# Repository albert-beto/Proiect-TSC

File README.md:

# InkTime v6

InkTime v6 este o platformă wearable construită pentru autonomie mare și interacțiune discretă. Dispozitivul folosește un display e-paper, conectivitate Bluetooth Low Energy, senzori de mișcare, feedback haptic și alimentare dintr-un acumulator LiPo încărcat prin USB-C.

La nivel de arhitectură, tot sistemul este orchestrat de un **Nordic nRF52840**, care gestionează radio-ul, magistralele digitale și logica de power management.

---

## Ce face dispozitivul

InkTime v6 este gândit ca un smartwatch sau dispozitiv portabil cu consum redus, capabil să rămână activ perioade lungi de timp între încărcări.

Funcțiile principale sunt:

- afișare pe e-paper, cu consum aproape nul în stare statică;
- comunicație BLE;
- detecție de mișcare și numărare pași;
- feedback haptic;
- încărcare prin USB-C;
- monitorizare a stării bateriei.

---

## Diagramă bloc

---

## Nucleul sistemului

### nRF52840

Controlerul principal este **nRF52840**, un SoC cu ARM Cortex-M4F, memorie Flash de 1 MB, 256 KB RAM, radio 2.4 GHz multiprotocol și interfață USB 2.0 Full-Speed integrată.

Acesta a fost ales pentru că permite integrarea într-un singur cip a mai multor funcții importante:

- comunicație BLE 5.0;
- control al perifericelor pe I2C și SPI;
- suport USB nativ;
- moduri eficiente de consum redus.

Pentru tactare sunt folosite două cristale externe:

- `X1` — 32 MHz, pentru **HFCLK**;
- `X2` — 32.768 kHz, pentru **LFCLK**.

---

## Interfețe și periferice

### Display e-paper

Interfața principală a utilizatorului este un display e-paper conectat printr-un FPC cu 24 de pini (`J3`). Pentru că afișajul este bistabil, energia este consumată în principal în timpul actualizării, nu în perioada în care imaginea rămâne neschimbată.

Controlul acestui bloc este împărțit în trei părți.

#### 1. Semnale digitale

Comunicarea cu displayul se face printr-o interfață SPI și linii auxiliare:

- `MOSI`
- `SCK`
- `EPD_CS`
- `EPD_DC`
- `EPD_RST`
- `EPD_BUSY`

#### 2. Tensiuni bias pentru panou

Driverul displayului are nevoie de mai multe tensiuni specifice pentru matricea TFT. Acestea sunt obținute cu ajutorul unui mic boost converter și al unei rețele de diode Schottky și condensatoare.

Tensiunile generate sunt:

- `VGH`
- `VGL`
- `VSH`
- `VSL`

#### 3. Oprirea completă a alimentării displayului

Alimentarea de 3.3 V a ansamblului EPD poate fi întreruptă complet printr-un load switch realizat cu MOSFET-ul P-channel **DMG2305UX** (`Q1`). Acesta este comandat de semnalul `EPD_PWR`.

### Accelerometru

Pentru detectarea activității este folosit **BMA423** (`IC2`), un accelerometru digital pe 3 axe.

Rolurile sale în proiect sunt:

- detecția de mișcare;
- step counting;
- generarea de evenimente prin întreruperi.

Componenta este utilizată în **mod I2C**, iar pinul `CSB` este conectat la `VDDIO` pentru a forța această configurație. Cele două ieșiri de întrerupere, `INT1` și `INT2`, sunt rutate separat spre microcontroller.

### Haptic

Blocul de feedback haptic se bazează pe **DRV2605** (`IC1`), controlat pe I2C. Activarea sau dezactivarea lui se face din semnalul `HAPTIC_EN`, conectat la un GPIO al MCU-ului.

Ieșirile `OUT+` și `OUT−` merg direct spre actuatorul haptic.

### Butoane

Sunt implementate trei butoane fizice:

- `SW_UP`
- `SW_DN`
- `SW_ENT`

Fiecare este conectat la câte un GPIO și are:

- pull-up extern de 10 kΩ;
- circuit RC de debounce cu 1 µF la GND.

---

## Alimentare

### USB-C

Conectorul `J1` este un **USB Type-C** (`KH-TYPE-C-16P`) folosit pentru alimentare și pentru conexiunea USB 2.0. În layout sunt rutate doar liniile necesare proiectului.

### Protecție ESD

Pentru protejarea liniilor USB și CC este folosit **USBLC6-2SC6Y**, plasat aproape de conector.

### Încărcător Li-Po

Gestionarea încărcării acumulatorului este făcută de **BQ25180** (`IC4`).

Acest circuit oferă:

- configurare prin I2C;
- curent de încărcare programabil;
- semnalizare de evenimente prin pinul `PMIC_INT`;
- protecție termică.

### Fuel gauge

Monitorizarea bateriei este realizată de **MAX17048** (`U1`), care măsoară tensiunea celulei și estimează nivelul de încărcare.

În design:

- comunică pe magistrala I2C comună;
- folosește semnalul `ALERT` pentru notificări către MCU.

### Convertor DC/DC

Subsistemul de putere include și **RT6160AWSC** (`IC3`), folosit ca convertor DC/DC.

---

## Programare și debug

Pentru flash și depanare este prevăzut un conector **Tag-Connect TC2030-IDC** (`J2`), cu 6 pini, fără header montat permanent pe PCB.

Liniile expuse sunt:

- `VTREF (3.3V)`
- `SWDIO`
- `SWDCLK`
- `SWO`
- `nRESET`
- `GND`

Pe placă există și test pads dedicate:

- `TP_SWDIO`
- `TP_SWDCLK`
- `TP_SWO`
- `TP_RESET`
- `TP_3.3V`
- `TP_GND`

---

## Alocarea pinilor MCU

Mai jos este rezumat mapping-ul relevant pentru nRF52840.

| Pin nRF52840 | Rol | Tip | Observație |
|---|---|---|---|
| **P0.00** | Cristal 32.768 kHz | OSC | Pin dedicat LFXO |
| **P0.01** | Cristal 32.768 kHz | OSC | Pin dedicat LFXO |
| **P0.09** | neconectat | GPIO | rezervat |
| **P0.10** | neconectat | GPIO | rezervat |
| **P0.13** | `MOSI` spre EPD | SPIM | rutare scurtă spre zona displayului |
| **P0.14** | `SCK` spre EPD | SPIM | grupat cu `MOSI` |
| **P0.18** | reset extern | nRESET | pin dedicat |
| **P0.19** | `EPD_CS` | SPIM | asociat interfeței EPD |
| **P0.20** | `EPD_DC` | GPIO | control display |
| **P0.21** | `EPD_RST` | GPIO | reset display |
| **P0.22** | `SWO` | SWO | debug |
| **P0.23** | `EPD_BUSY` | GPIO input + INT | semnal status display |
| **P0.24** | `EPD_PWR` | GPIO | comandă load switch |
| **P0.25** | `HAPTIC_EN` | GPIO | enable pentru DRV2605 |
| **P0.26** | `SDA` | TWIM | magistrală I2C |
| **P0.27** | `SCL` | TWIM | magistrală I2C |
| **P0.28** | neconectat | analog | rezervat |
| **P0.29** | neconectat | GPIO | rezervat |
| **P0.30** | neconectat | GPIO | rezervat |
| **P0.31** | neconectat | GPIO | rezervat |
| **P1.00** | `PMIC_INT` | GPIO input + INT | evenimente de charging |
| **P1.01** | `SW_UP` | GPIO input | buton |
| **P1.02** | `SW_DN` | GPIO input | buton |
| **P1.03** | `SW_ENT` | GPIO input | buton |
| **P1.04** | `IMU_INT1` | GPIO input + INT | eveniment accelerometru |
| **P1.05** | `IMU_INT2` | GPIO input + INT | eveniment accelerometru |
| **P1.06** | `ALERT` | GPIO input + INT | alertă baterie |
| **P1.07** | EPD spre Q3 | GPIO / PWM | comandă auxiliară |
| **SWDCLK** | programare / debug | dedicat | SWD |
| **SWDIO** | programare / debug | dedicat | SWD |
| **VBUS** | detectare USB | USB PHY | sensing VBUS |
| **D+ / D−** | USB 2.0 FS | USB PHY | interfață USB |

---

## Consum și autonomie

### Curent estimat în standby

| Componentă | Curent tipic | Observații |
|---|---:|---|
| nRF52840 (System ON, RAM retention, RTC, LFXO) | ~1.5 µA | radio inactiv |
| BMA423 (low-power, 25 Hz) | ~4 µA | step detection activ |
| BQ25180 (quiescent, no charge) | ~6 µA | |
| MAX17048 (active measurement) | ~23 µA | hibernate ~3 µA |
| DRV2605 (EN=LOW) | < 1 µA | shutdown |
| RT6160 (PFM, fără sarcină) | ~25 µA | ultra-low-quiescent |
| E-paper | ~0 µA | fără refresh |
| Leakage PCB + diode | ~5 µA | estimat |
| **Total** | **≈ 65 µA** | |

### Autonomie estimată pentru 150 mAh

Presupunând un profil de utilizare tipic:

- 23 h 45 min standby la 65 µA → aproximativ 1.54 mAh/zi;
- refresh-uri de ecran → aproximativ 0.2 mAh/zi;
- evenimente haptice → aproximativ 0.01 mAh/zi.

Consum total zilnic estimat:

**≈ 1.75 mAh/zi**

Autonomie rezultată:

**150 mAh / 1.75 mAh pe zi ≈ 85 zile**

---

## Note de implementare

În faza curentă de proiect au fost acceptate câteva compromisuri și excepții:

- pentru rezistoare și condensatoare mici au fost păstrate modele 3D placeholder;
- au fost aprobate 6 erori legate de modelele 3D ale butoanelor;
- au fost acceptate erori de tip **Overlap** și **Copper clearance** asociate utilizării tehnicii **via-in-pad**.

---

## Concluzie tehnică

InkTime v6 este un sistem compact orientat spre consum redus, în care displayul bistabil, BLE-ul, senzorii și managementul de putere sunt integrate în jurul nRF52840. Arhitectura a fost gândită pentru un dispozitiv portabil capabil să ofere autonomie mare, funcții utile de interacțiune și o interfață modernă cu utilizatorul.

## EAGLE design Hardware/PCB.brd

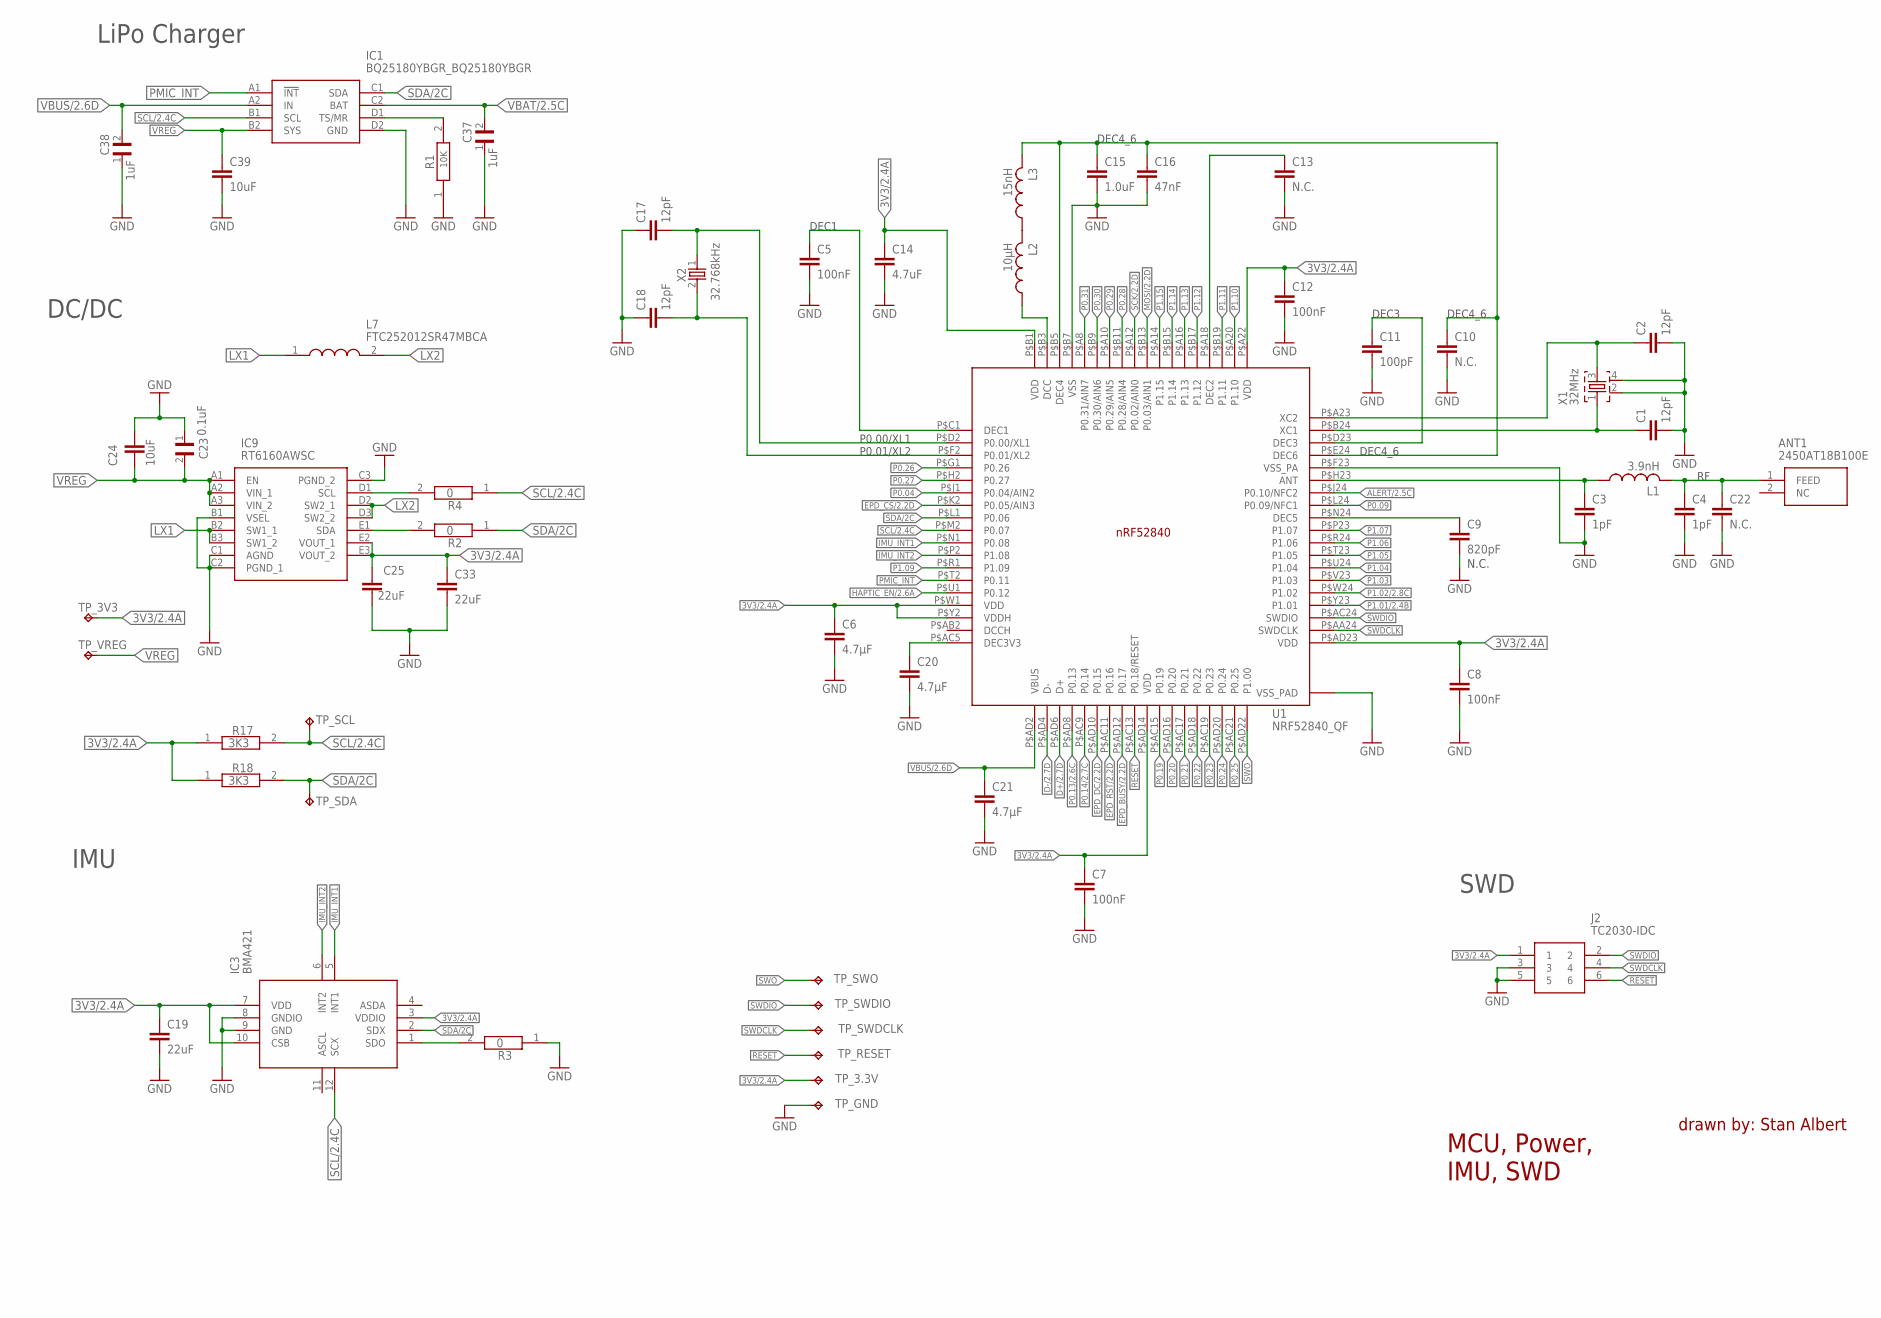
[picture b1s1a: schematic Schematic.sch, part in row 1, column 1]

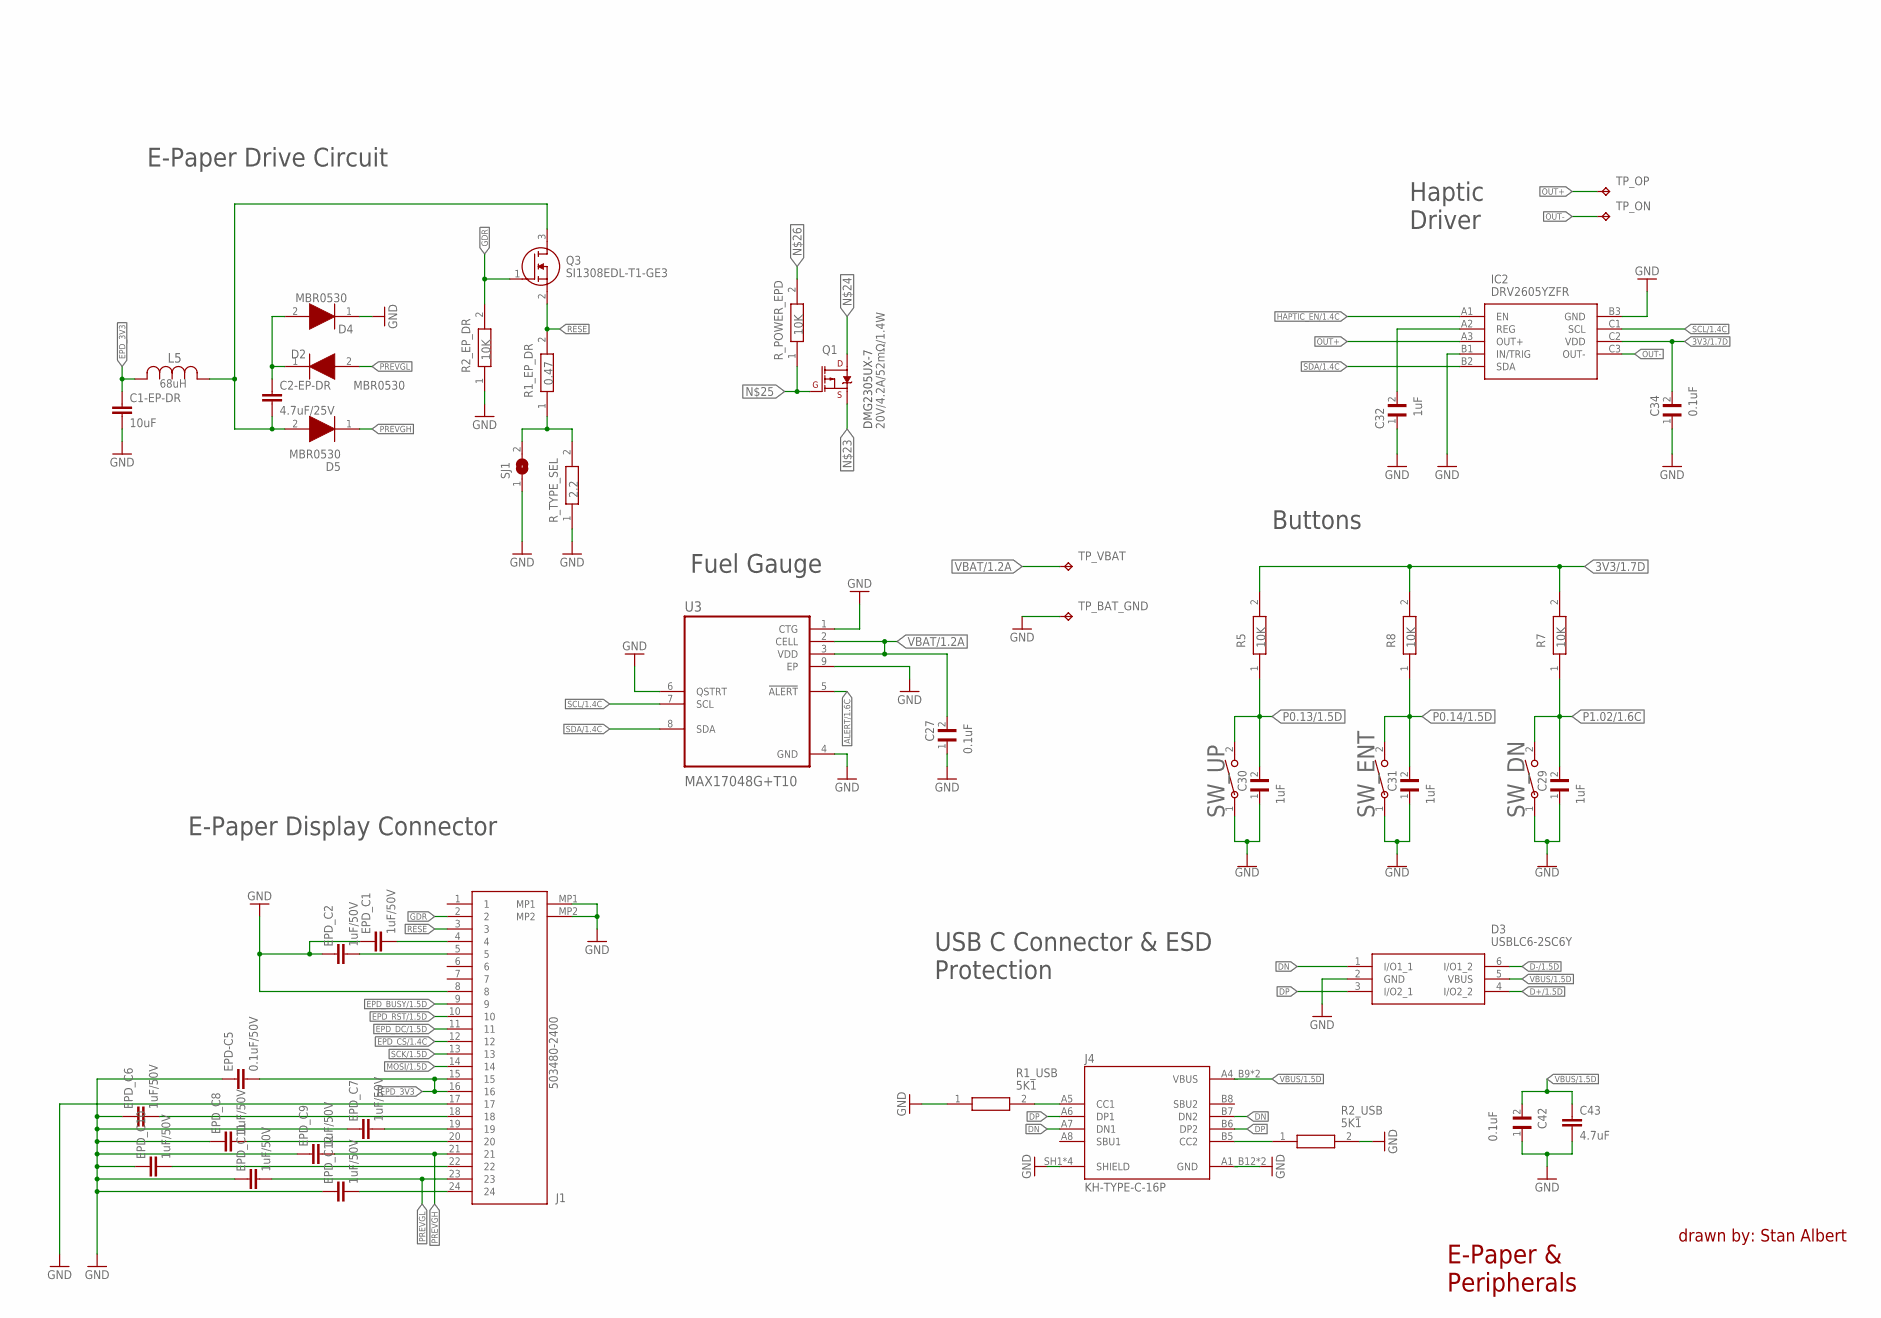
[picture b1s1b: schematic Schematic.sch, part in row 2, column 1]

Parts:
ANT1: 2450AT18B100E; 2450AT18B100E_ANTC3216X140N
C1, C2, C17, C18: 12pF; NORDIC_NRF_3_RESC0201_L
C1-EP-DR, C24, C39: 10uF; NORDIC_NRF_3_RESC0402_L
C2-EP-DR: 4.7uF/25V; NORDIC_NRF_3_RESC0402_L
C3, C4: 1pF; NORDIC_NRF_3_RESC0201_L
C5, C7, C8, C12: 100nF; NORDIC_NRF_3_RESC0201_L
C6, C20, C21: 4.7µF; NORDIC_NRF_3_RESC0402_L
C9: 820pF; NORDIC_NRF_3_RESC0201_L
C10, C13, C22: N.C.; NORDIC_NRF_3_RESC0201_L
C11: 100pF; NORDIC_NRF_3_RESC0201_L
C14, C43: 4.7uF; NORDIC_NRF_3_RESC0402_L
C15: 1.0uF; NORDIC_NRF_3_RESC0402_L
C16: 47nF; NORDIC_NRF_3_RESC0201_L
C19, C33: 22uF; NORDIC_NRF_3_RESC0201_L
C23, C27, C34, C42: 0.1uF; GRM011R60J152KE01L_2_CAPC0201X13N
C25: 22uF; NORDIC_NRF_3_RESC0402_L
C29, C30, C31, C32, C37, C38: 1uF; GRM011R60J152KE01L_2_CAPC0201X13N
D2, D4, D5: MBR0530; ESP32_C6_LIBRARY_5_SOD3716X135N
D3: USBLC6-2SC6Y; ESP32_C6_LIBRARY_3_SOT95P280X145-6N
EPD-C5: 0.1uF/50V; NORDIC_NRF_3_RESC0201_L
EPD_C1, EPD_C2, EPD_C6, EPD_C7, EPD_C8, EPD_C9, EPD_C10, EPD_C11, EPD_C12: 1uF/50V; NORDIC_NRF_3_RESC0402_L
IC1: BQ25180YBGR_BQ25180YBGR; BQ25180YBGR_BGA8C40P2X4_100X155X50
IC2: DRV2605YZFR; DRV2605YZFR_BGA9C50P3X3_144X144X62
IC3: BMA421; BMA423_BMA423
IC9: RT6160AWSC; RT6160AWSC_BGA15C40P3X5_140X230X60
J1: 503480-2400; 503480-2400_5034802400
J2: TC2030-IDC; TC2030-IDC_TC2030IDC
J4: KH-TYPE-C-16P; KH-TYPE-C-16P_KINGHELM_KH-TYPE-C-16P
L1: 3.9nH; NORDIC_NRF_2_RESC0402_L
L2: 10µH; NORDIC_NRF_2_RESC0402_L
L3: 15nH; NORDIC_NRF_2_RESC0402_L
L5: 68uH; ESP32_C6_LIBRARY_2_IND_4828-WE-TPC_WRE
L7: FTC252012SR47MBCA; MLP2016SR47MT0S1_INDC2016X100N
Q1: 20V/4.2A/52mΩ/1.4W; ESP32_C6_LIBRARY_4_ESP32_C6_LIBRARY_4_ESP32_C6_LIBRARY_4_ES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
Q3: SI1308EDL-T1-GE3; ESP32_C6_LIBRARY_6_SOT65P210X110-3N
R1: 10K; ERA-1AEB3401C_0201
R1_EP_DR: 0.47; CPF0201D7K68C1_0201
R1_USB, R2_USB: 5K1; CPF0201D7K68C1_0201
R2, R3, R4: 0; CPF0201D7K68C1_0201
R2_EP_DR, R5, R7, R8: 10K; CPF0201D7K68C1_0201
R17, R18: 3K3; CPF0201D7K68C1_0201
R_POWER_EPD: 10K; CPF0201D7K68C1_0201
R_TYPE_SEL: 2.2; CPF0201D7K68C1_0201
SJ1: ESP32_C6_LIBRARY_7_JUMPER_SJ
SW_DN: 2025-10-22_07-23-44_LIBRARY_EVP-AKE31ASW_EVP-AKE3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; 2025-10-22_07-23-44_LIBRARY_SW_EVP-AKE31A_PAN
SW_ENT: 2025-10-22_07-23-44_LIBRARY_EVP-AKE31ASW_EVP-AKE3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; 2025-10-22_07-23-44_LIBRARY_SW_EVP-AKE31A_PAN
SW_UP: 2025-10-22_07-23-44_LIBRARY_EVP-AKE31ASW_EVP-AKE3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; 2025-10-22_07-23-44_LIBRARY_SW_EVP-AKE31A_PAN
TP_3.3V, TP_3V3: HECTOR_WATCH_1_TPTP20R; HECTOR_WATCH_1_TP20R
TP_BAT_GND: HECTOR_WATCH_1_TPTP20R; HECTOR_WATCH_1_TP20R
TP_GND: HECTOR_WATCH_1_TPTP20R; HECTOR_WATCH_1_TP20R
TP_ON: HECTOR_WATCH_1_TPTP20R; HECTOR_WATCH_1_TP20R
TP_OP: HECTOR_WATCH_1_TPTP20R; HECTOR_WATCH_1_TP20R
TP_RESET: HECTOR_WATCH_1_TPTP20R; HECTOR_WATCH_1_TP20R
TP_SCL: HECTOR_WATCH_1_TPTP20R; HECTOR_WATCH_1_TP20R
TP_SDA: HECTOR_WATCH_1_TPTP20R; HECTOR_WATCH_1_TP20R
TP_SWDCLK: HECTOR_WATCH_1_TPTP20R; HECTOR_WATCH_1_TP20R
TP_SWDIO: HECTOR_WATCH_1_TPTP20R; HECTOR_WATCH_1_TP20R
TP_SWO: HECTOR_WATCH_1_TPTP20R; HECTOR_WATCH_1_TP20R
TP_VBAT: HECTOR_WATCH_1_TPTP20R; HECTOR_WATCH_1_TP20R
TP_VREG: HECTOR_WATCH_1_TPTP20R; HECTOR_WATCH_1_TP20R
U1: NRF52840_QF; NORDIC_NRF_4_AQFN50P700X700X85_HS-74N
U3: MAX17048G+T10; ESP32_C6_LIBRARY_SON50P200X200X80-9N
X1: 32MHz; NORDIC_NRF_BT-XTAL_2016_N
X2: 32.768kHz; NORDIC_NRF_1_XTAL_3215_N

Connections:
3V3/1.7D: C34.2, IC2.C2 (VDD), R5.2, R7.2, R8.2
3V3/2.4A: C6.1, C7.1, C8.1, C12.1, C14.1, C19.1, C25.1, C33.1, IC3.3 (VDDIO), IC3.7 (VDD), IC3.10 (CSB), IC9.E2 (VOUT_1), IC9.E3 (VOUT_2), J2.1, R17.1, R18.1, TP_3.3V.TP, TP_3V3.TP, U1.P$A22 (VDD), U1.P$AD14 (VDD), U1.P$AD23 (VDD), U1.P$B1 (VDD), U1.P$W1 (VDD), U1.P$Y2 (VDDH)
10K: IC1.D1 (TS/MR), R1.2
ALERT/1.6C: U3.5 (!ALERT)
ALERT/2.5C: U1.P$J24 (P0.10/NFC2)
D+/1.5D: D3.4 (I/O2_2)
D+/2.7D: U1.P$AD6 (D+)
D-/1.5D: D3.6 (I/O1_2)
D-/2.7D: U1.P$AD4 (D-)
DN: D3.1 (I/O1_1), J4.A7 (DN1), J4.B7 (DN2)
DP: D3.3 (I/O2_1), J4.A6 (DP1), J4.B6 (DP2)
EPD_3V3: C1-EP-DR.1, EPD-C5.2, J1.15, J1.16, L5.2
EPD_BUSY/1.5D: J1.9
EPD_BUSY/2.2D: U1.P$AD12 (P0.17)
EPD_CS/1.4C: J1.12
EPD_CS/2.2D: U1.P$K2 (P0.05/AIN3)
EPD_DC/1.5D: J1.11
EPD_DC/2.2D: U1.P$AD10 (P0.15)
EPD_RST/1.5D: J1.10
EPD_RST/2.2D: U1.P$AC11 (P0.16)
GDR: J1.2, Q3.1 (G), R2_EP_DR.2
GND: C1.2, C1-EP-DR.2, C2.2, C3.2, C4.2, C5.2, C6.2, C7.2, C8.2, C9.2, C10.2, C11.2, C12.2, C13.2, C14.2, C15.2, C16.2, C17.1, C18.1, C19.2, C20.2, C21.2, C22.2, C23.1, C24.1, C25.2, C27.1, C29.1, C30.1, C31.1, C32.1, C33.2, C34.1, C37.1, C38.1, C39.2, C42.1, C43.2, D3.2 (GND), D4.1 (K), EPD-C5.1, EPD_C1.1, EPD_C2.1, EPD_C6.1, EPD_C7.1, EPD_C8.1, EPD_C9.1, EPD_C10.1, EPD_C11.1, EPD_C12.1, IC1.D2 (GND), IC2.B1 (IN/TRIG), IC2.B3 (GND), IC3.8 (GNDIO), IC3.9 (GND), IC9.B1 (VSEL), IC9.C1 (AGND), IC9.C2 (PGND_1), IC9.C3 (PGND_2), J1.8, J1.17, J1.MP1, J1.MP2, J2.3, J2.5, J4.A1_B12 (GND), J4.A12_B1 (GND), J4.SH1 (SHIELD), J4.SH2 (SHIELD), J4.SH3 (SHIELD), J4.SH4 (SHIELD), R1.1, R1_USB.1, R2_EP_DR.1, R2_USB.2, R3.1, R_TYPE_SEL.1, SJ1.1, SW_DN.1, SW_ENT.1, SW_UP.1, TP_BAT_GND.TP, TP_GND.TP, U1.P$74 (VSS_PAD), U1.P$75 (VSS_PAD), U1.P$76 (VSS_PAD), U1.P$77 (VSS_PAD), U1.P$78 (VSS_PAD), U1.P$79 (VSS_PAD), U1.P$80 (VSS_PAD), U1.P$81 (VSS_PAD), U1.P$82 (VSS_PAD), U1.P$83 (VSS_PAD), U1.P$84 (VSS_PAD), U1.P$85 (VSS_PAD), U1.P$86 (VSS_PAD), U1.P$87 (VSS_PAD), U1.P$88 (VSS_PAD), U1.P$89 (VSS_PAD), U1.P$90 (VSS_PAD), U1.P$B7 (VSS), U1.P$F23 (VSS_PA), U3.1 (CTG), U3.4 (GND), U3.6 (QSTRT), U3.9 (EP), X1.2, X1.4
HAPTIC_EN/1.4C: IC2.A1 (EN)
HAPTIC_EN/2.6A: U1.P$U1 (P0.12)
IMU_INT1: IC3.5 (INT1), U1.P$N1 (P0.08)
IMU_INT2: IC3.6 (INT2), U1.P$P2 (P1.08)
LX1: IC9.B2 (SW1_1), IC9.B3 (SW1_2), L7.1
LX2: IC9.D2 (SW2_1), IC9.D3 (SW2_2), L7.2
MOSI/1.5D: J1.14
MOSI/2.2D: U1.P$B13 (P0.03/AIN1)
unnamed: IC9.D1 (SCL), R4.2
unnamed: IC3.1 (SDO), R3.2
unnamed: C9.1, U1.P$N24 (DEC5)
unnamed: IC9.E1 (SDA), R2.2
unnamed: C20.1, U1.P$AC5 (DEC3V3)
unnamed: C3.1, L1.1, U1.P$H23 (ANT)
unnamed: ANT1.1 (FEED), C4.1, C22.1, L1.2
unnamed: C1.1, U1.P$B24 (XC1), X1.1
unnamed: C2.1, U1.P$A23 (XC2), X1.3
unnamed: C13.1, U1.P$A18 (DEC2)
unnamed: C11.1, U1.P$D23 (DEC3)
unnamed: C10.1, C15.1, C16.1, L3.2, U1.P$B5 (DEC4), U1.P$E24 (DEC6)
unnamed: L2.1, U1.P$B3 (DCC)
unnamed: L2.2, L3.1
unnamed: C5.1, U1.P$C1 (DEC1)
unnamed: C17.2, U1.P$D2 (P0.00/XL1), X2.1
unnamed: C2-EP-DR.2, D5.2 (A), L5.1, Q3.3 (D)
unnamed: C18.2, U1.P$F2 (P0.01/XL2), X2.2
unnamed: C2-EP-DR.1, D2.1 (K), D4.2 (A)
unnamed: R1_EP_DR.1, R_TYPE_SEL.2, SJ1.2
unnamed: Q1.1 (G), R_POWER_EPD.1
unnamed: EPD_C1.2, J1.4
unnamed: EPD_C2.2, J1.5
unnamed: EPD_C6.2, J1.18
unnamed: J4.B5 (CC2), R2_USB.1
unnamed: EPD_C7.2, J1.19
unnamed: C32.2, IC2.A2 (REG)
unnamed: EPD_C8.2, J1.20
unnamed: J4.A5 (CC1), R1_USB.2
unnamed: EPD_C10.2, J1.22
unnamed: EPD_C12.2, J1.24
OUT+: IC2.A3 (OUT+)
OUT-: IC2.C3 (OUT-)
P0.04: U1.P$J1 (P0.04/AIN2)
P0.09: U1.P$L24 (P0.09/NFC1)
P0.13/1.5D: C30.2, R5.1, SW_UP.2
P0.13/2.6C: U1.P$AD8 (P0.13)
P0.14/1.5D: C31.2, R8.1, SW_ENT.2
P0.14/2.7C: U1.P$AC9 (P0.14)
P0.19: U1.P$AC15 (P0.19)
P0.20: U1.P$AD16 (P0.20)
P0.21: U1.P$AC17 (P0.21)
P0.22: U1.P$AD18 (P0.22)
P0.23: U1.P$AC19 (P0.23)
P0.24: U1.P$AD20 (P0.24)
P0.25: U1.P$AC21 (P0.25)
P0.26: U1.P$G1 (P0.26)
P0.27: U1.P$H2 (P0.27)
P0.28: U1.P$B11 (P0.28/AIN4)
P0.29: U1.P$A10 (P0.29/AIN5)
P0.30: U1.P$B9 (P0.30/AIN6)
P0.31: U1.P$A8 (P0.31/AIN7)
P1.01/2.4B: U1.P$Y23 (P1.01)
P1.02/1.6C: C29.2, R7.1, SW_DN.2
P1.02/2.8C: U1.P$W24 (P1.02)
P1.03: U1.P$V23 (P1.03)
P1.04: U1.P$U24 (P1.04)
P1.05: U1.P$T23 (P1.05)
P1.06: U1.P$R24 (P1.06)
P1.07: U1.P$P23 (P1.07)
P1.09: U1.P$R1 (P1.09)
P1.10: U1.P$A20 (P1.10)
P1.11: U1.P$B19 (P1.11)
P1.12: U1.P$B17 (P1.12)
P1.13: U1.P$A16 (P1.13)
P1.14: U1.P$B15 (P1.14)
P1.15: U1.P$A14 (P1.15)
PMIC_INT: IC1.A1 (!INT), U1.P$T2 (P0.11)
PREVGH: D5.1 (K), EPD_C9.2, J1.21
PREVGL: D2.2 (A), EPD_C11.2, J1.23
RESE: J1.3, Q3.2 (S), R1_EP_DR.2
RESET: J2.6, TP_RESET.TP, U1.P$AC13 (P0.18/RESET)
SCK/1.5D: J1.13
SCK/2.2D: U1.P$A12 (P0.02/AIN0)
SCL/1.4C: IC2.C1 (SCL), U3.7 (SCL)
SCL/2.4C: IC1.B1 (SCL), IC3.12 (SCX), R4.1, R17.2, TP_SCL.TP, U1.P$M2 (P0.07)
SDA/1.4C: IC2.B2 (SDA), U3.8 (SDA)
SDA/2C: IC1.C1 (SDA), IC3.2 (SDX), R2.1, R18.2, TP_SDA.TP, U1.P$L1 (P0.06)
SWDCLK: J2.4, TP_SWDCLK.TP, U1.P$AA24 (SWDCLK)
SWDIO: J2.2, TP_SWDIO.TP, U1.P$AC24 (SWDIO)
SWO: TP_SWO.TP, U1.P$AD22 (P1.00)
VBAT/1.2A: C27.2, TP_VBAT.TP, U3.2 (CELL), U3.3 (VDD)
VBAT/2.5C: C37.2, IC1.C2 (BAT)
VBUS/1.5D: C42.2, C43.1, D3.5 (VBUS), J4.A4_B9 (VBUS), J4.A9_B4 (VBUS)
VBUS/2.6D: C21.1, C38.2, IC1.A2 (IN), U1.P$AD2 (VBUS)
VREG: C23.2, C24.2, C39.1, IC1.B2 (SYS), IC9.A1 (EN), IC9.A2 (VIN_1), IC9.A3 (VIN_2), TP_VREG.TP

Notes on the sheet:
LiPo Charger
DC/DC
IMU
N.C.
SWD
DEC3
DEC4_6
DEC1
P0.00/XL1
P0.01/XL2
MCU, Power, IMU, SWD
drawn by: Stan Albert
E-Paper Drive Circuit
DMG2305UX-7
Fuel Gauge
Haptic Driver
Buttons
USB C Connector & ESD Protection
E-Paper Display Connector
E-Paper & Peripherals

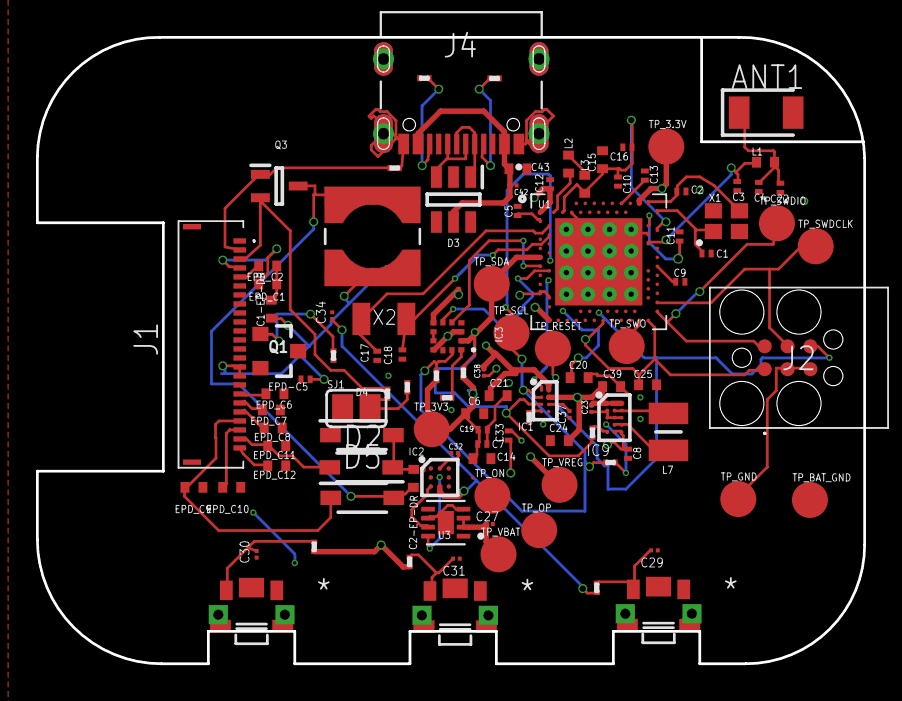
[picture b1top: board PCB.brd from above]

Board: 4 copper layers, 46.0 x 34.8 mm, 105 parts (0 on the bottom side), 63 nets.

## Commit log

2026-04-14 Manufacturing stage
2026-04-14 Hardware
2026-04-19 PCB v2
2026-04-19 Images
2026-04-19 Mechanical Stage
2026-04-19 PCB v3
2026-04-19 Revise README for InkTime v6 project details
    Updated README.md to enhance project description and hardware details.
2026-04-19 Added Diagram
2026-04-19 Revise README.md for InkTime v6 details

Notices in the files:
parts and their libraries:
COPYRIGHT: Copyright (C) 2024 Ultra Librarian. All rights reserved.
COPYRIGHT: Copyright (C) 2025 Ultra Librarian. All rights reserved.
